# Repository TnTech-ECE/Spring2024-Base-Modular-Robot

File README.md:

# Modular IEEE Robot

## Executive Summary

Each year, Tennessee Technological University (Tech) participates in the Institute of Electrical and Electronics Engineers (IEEE) Southeastern Conference (SECON) hardware competition. The competition asks participants to create a robot that can perform various tasks, and competitors are scored based on their robot’s capability to complete tasks as quickly as possible. In past years, Tech has placed well, but the same problems have arisen each year that have inhibited wins: choppy navigation, shorted cables, and battery depletion are just a few of the many problems teams have repeatedly faced in previous competitions. The team sets out to fix the besetting problems that teams face each year not by competing in SECON, but rather by building a generalized platform that will optimize the basic robotic functionality for future teams. Sensing, movement, and centralized charging are the top priorities in the team’s design, all fitted together in a modular, adaptable framework that can be manipulated to fit most – if not all – IEEE hardware competition specifications. No longer will teams have to spend countless hours learning and designing movement systems or hoping everything works after rewiring a battery mid-competition. The design will take care of these basic competition necessities and leave the custom tailoring to the competition team.  

## Capabilities

The current version of the robot has the following capabilities:
1. Autonomous navigation
2. Modular components that can be easily adapted for different uses
3. Robust, centralized charging system
4. Functioning emergency stop button
5. Can travel inclines and declines up to 25 degrees
7. 360 degrees of movement
8. Knows location within a 2 inch tolerance
9. Sensors are are plug and play adpatable with the use of an I2C bus
10. Foundation layed for autonomous navgivaton with LiDAR and ROS2
11. User manual for teams to understand design considerations, common problems, and solutions

## Salient Outcomes

As projects progress, there are typically outcomes tht are more impressive than others. Here is a list of salient outcomes of this project:
1. Wireless charging proof of concept
2. Multiple navigation subsets for teams to choose between
3. Foundation for layed for ROS2 mapping for future uses
4. Plug and play adapatibility with sensors through I2C buses
5. Power board with ground isolation
6. GUI for teams to see their live data transmission 

## Project Demonstration & Images

3D model of the robot vs the final product

[Watch the video](https://youtu.be/stM9KGa8I_E) of the robot autonomously navigating a line.

[Watch the video](https://youtu.be/3MeIy1WahUA) of the robot autonomously sweeping the board given its location.

[Watch the video](https://youtu.be/3MeIy1WahUA](https://www.youtube.com/watch?v=_iFhnvbLboQ)) of the robot detecting objects in front of it.

## About Us

### Team

**[Luke Chapman](https://www.linkedin.com/in/luke-chapman-/)** is an electrical engineering major at Tennessee Technological University with a minor in mathematics. He is interested in electromagnetics, telecommunications, and signal processing. Luke is responsible for the power management and distribution systems of the robot as well as the experimental wireless power charging system.

**[Reid Crews](https://www.linkedin.com/in/jackson-crews-381187257/)** is an electrical engineering major, mechatronics concentration at Tennessee Technological University with a minor in mathematics. Reid's interests are mechatronics and control systems. For the project, Reid is a contributor for the navigation sensing, primarily the location and object detection subsystems.

**[Isaac Hoese](https://www.linkedin.com/in/isaac-hoese-425748251)** is a senior electrical engineering student from Greeneville, Tn. He is interested in both power system analysis and embedded system design. In this project, Isaac will be a contributor for the navigation sensing, primarily the line following and orientation subsystems.

**[Isaac Jennings](www.linkedin.com/in/isaac-jennings-a04680209)** is a senior electrical engineering student with a minor in mathematics from Church Hill, TN. He takes interest in control systems, programming, and embedded systems, which is where he allocated his time by working on the master control systems on the project. He is responsible for the navigation and localization of the robot as it interfaces with the game board.  

**[Abigail Kennedy](https://www.linkedin.com/in/abigail-kennedy-tech/)** is an electrical engineering major at Tennessee Technological University with minors in mathematics and education. Abigail's primary interest is in controls and PLC design, and for this project, she worked on the motor control subsystem to ensure the robot can move quickly and smoothly.

**[Mabel Olson](https://www.linkedin.com/in/mabelolson/)** is an electrical engineering major at Tennessee Technological University with a minor in mathematics. She is intrested in power and control systems. In this project, Mabel is responsible for the chassis design, robot layout, organization, and any 3D designing of component attachment pieces. 

### Faculty Supervisor

The faculty supervisor for this project is [Dr. Nan Chen][def1]. She completed her electrical and control engineering Bachelor's degree from Nanjing University of Aeronautics and Astronautics. She also completed her Master's and Ph.D. in electrical engineering from the University of Waterloo. 

[def1]: https://www.linkedin.com/in/nan-chen-319aa185/

### Stakeholders

The primary customer for the project is [Professor Jesse Roberts](https://www.linkedin.com/in/jessetnroberts/) - the advisor for the IEEE SECON hardware teams. Future teams are impacted by this design but unable to be stakeholders, so he gives input on their behalf based on his years of experience with the competition.

### Recognitions

We would like to recognize and thank Professor Jesse Roberts, Dr. Nan Chen, and Dr. Charles Van Neste for their continuous input and guidance on the project.

## Repo Organization

### [Reports](/Reports)

The [Project Proposal](./Reports/Project%20Proposal/Project%20Proposal%20Revised.pdf) is the initial document for the project where the problem is defined and the goals for the project.

The [Conceptual Design](./Reports/Conceptual%20Design/Conceptual%20Design%20and%20Planning%20V2.pdf) gives a more detailed solution to the problem as well as subsystem breakdowns and a projected timeline and budget.

The [Experimentation](/Documentation/Experimental%20Analysis) gives the experimental results of the different subsystems and how constraints were met or not.

The [Poster](./Reports/Poster/Modular%20IEEE%20Robot%20Poster.pdf) is what the team presented at the 2024 capstone showcase.

The [Final Presentation](./Reports/Final%20Presentation/Final%20Presentation.pdf) is the presentation that the team gave to the IAB.

The [Lessons Learned](./Reports/LessonsLearnedAndAquiredSkills.md) gives team members' reflections on their progress, oversights, noteable incidents, and successes.

### [Documentation](/Documentation)
All documentation for the project is included in the above folder. Documentation includes all schematics, images, models, BOM, and designs used in the project.

The [Meeting Minutes](/Documentation/Meeting%20Minutes) folder contains the dated minutes from weekly meetings and allows a quick view into the progress of the team.

[Signoffs](/Documentation/Signoffs) are used to finalize designs for each subsystem. This includes schematics, design decisions, BOM, and analysis. 

### [Software](/Software)

 All software used and created is listed in the [Software](./Software) directory. For each subsystem, there are specific folders listed to find the necessary code.

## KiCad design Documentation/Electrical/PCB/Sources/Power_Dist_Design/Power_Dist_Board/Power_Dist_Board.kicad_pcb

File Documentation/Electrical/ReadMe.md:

This directory contains all of the electrical schematics and PCB files. The PCB directory contains files for the simulation, schematics, and design of the power distribution PCB. The Schematics directory contains the files for the Arduino schematic. The Testing directory contains data from testing the battery life and some notes taken while performing tests on the different power subsystems.

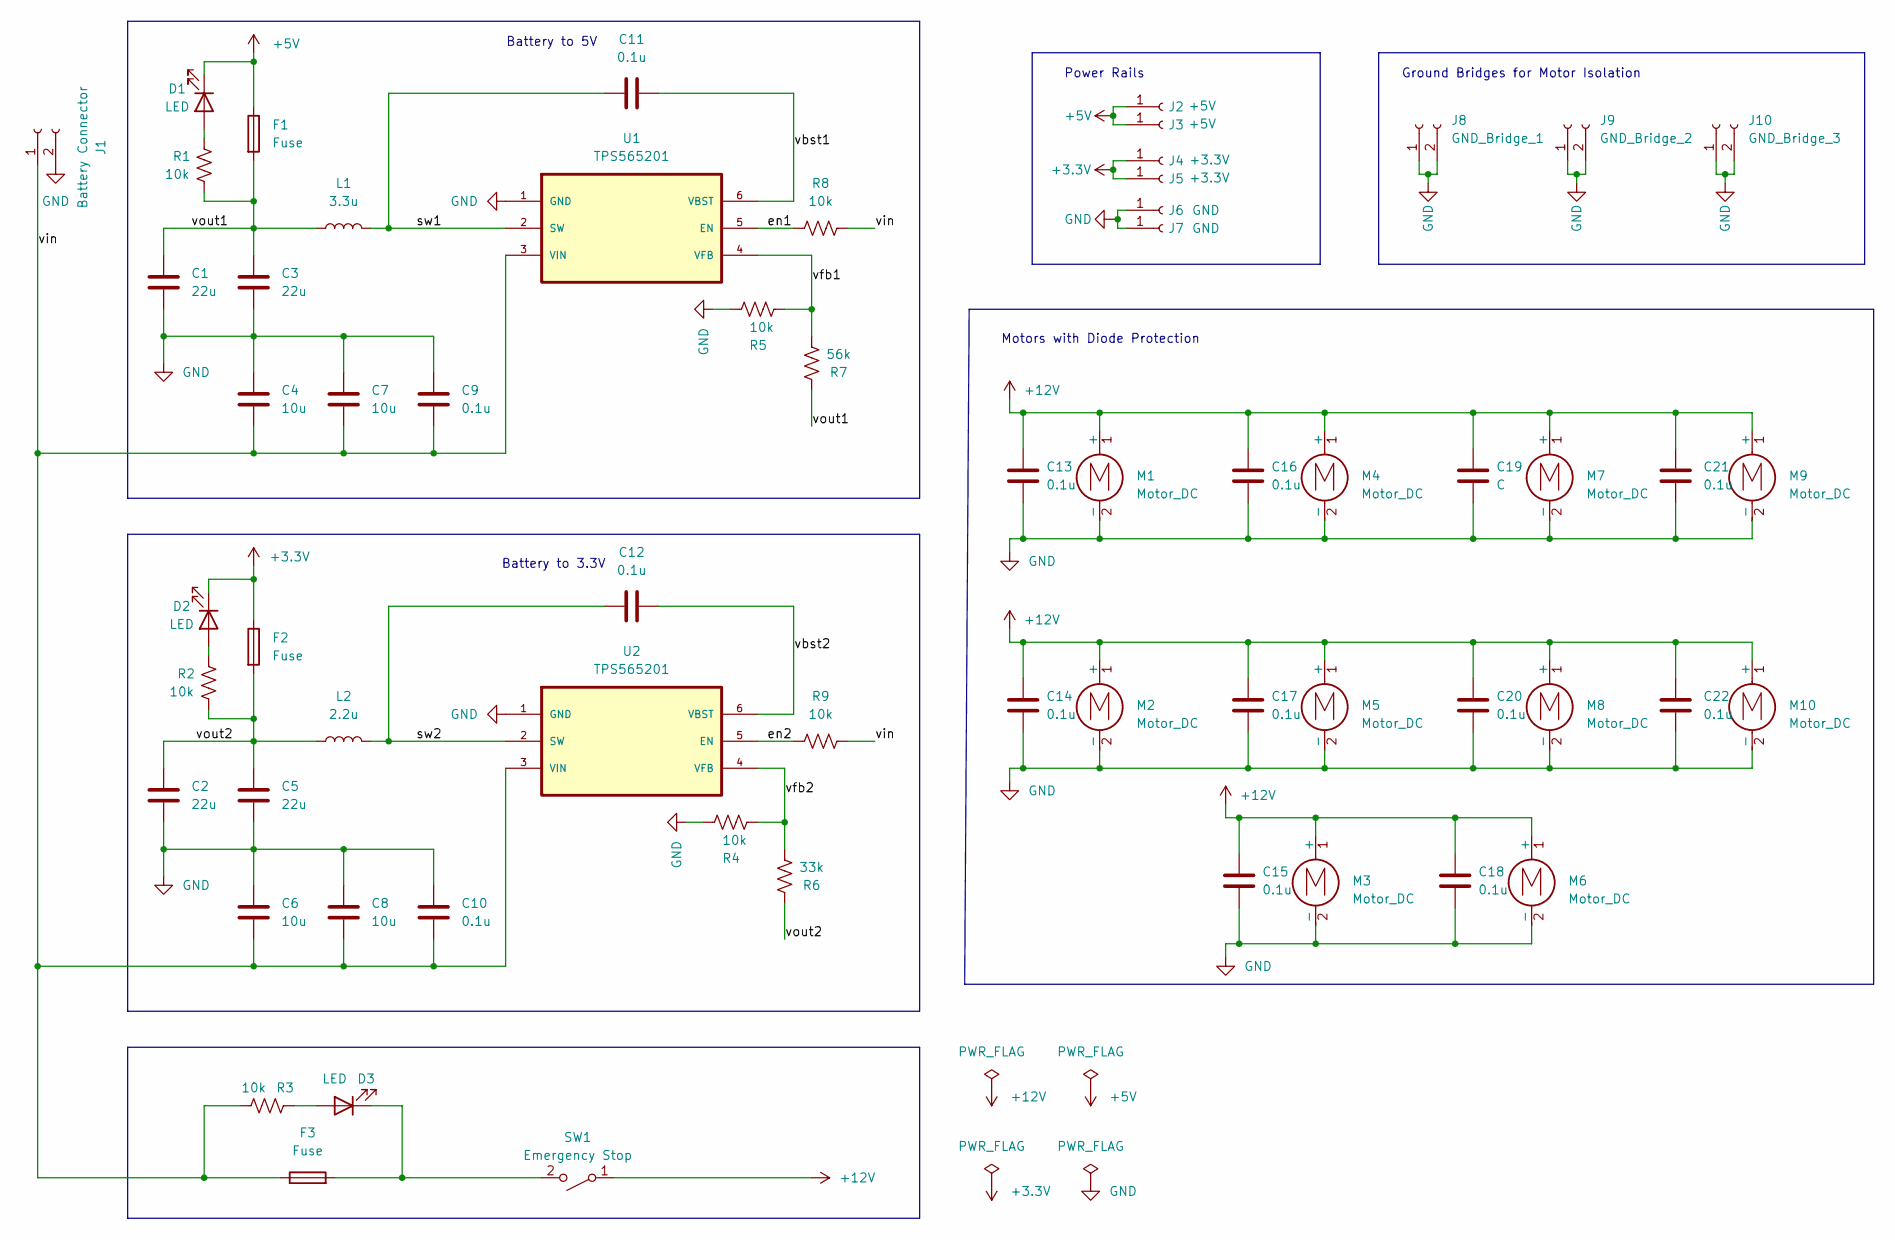
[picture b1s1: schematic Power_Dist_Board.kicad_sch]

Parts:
C1, C2, C3, C5: 22u; C_1206_3216Metric_Pad1.33x1.80mm_HandSolder
C4, C6, C7, C8: 10u; C_1206_3216Metric_Pad1.33x1.80mm_HandSolder
C9, C10, C11, C12, C13, C14, C15, C16, C17, C18, C20, C21, C22: 0.1u; C_1206_3216Metric_Pad1.33x1.80mm_HandSolder
C19: C; C_1206_3216Metric_Pad1.33x1.80mm_HandSolder
D1, D2, D3: LED; LED_1206_3216Metric_Pad1.42x1.75mm_HandSolder
F1, F2, F3: Fuse; Fuse_1206_3216Metric_Pad1.42x1.75mm_HandSolder
J1: Battery Connector; Molex_Screw_Term_0397730002
J2, J3: +5V; Pwr_Rail_Conn_Custom
J4, J5: +3.3V; Pwr_Rail_Conn_Custom
J6, J7: GND; Pwr_Rail_Conn_Custom
J8: GND_Bridge_1; GND_Bridge
J9: GND_Bridge_2; GND_Bridge
J10: GND_Bridge_3; GND_Bridge
L1: 3.3u; IND_SPM6530_TDK
L2: 2.2u; IND_SPM6530_TDK
M1, M2, M3, M4, M5, M6, M7, M8, M9, M10: Motor_DC; Molex_Screw_Term_0397730002
R1, R2, R3, R4, R5, R8, R9: 10k; R_1206_3216Metric_Pad1.30x1.75mm_HandSolder
R6: 33k; R_1206_3216Metric_Pad1.30x1.75mm_HandSolder
R7: 56k; R_1206_3216Metric_Pad1.30x1.75mm_HandSolder
SW1: Emergency Stop; Molex_Screw_Term_0397730002
U1, U2: TPS565201

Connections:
+3.3V: D2.1 (K), F2.1, J4.1, J5.1
+5V: D1.1 (K), F1.1, J2.1, J3.1
+12V: C13.1, C14.1, C15.1, C16.1, C17.1, C18.1, C19.1, C20.1, C21.1, C22.1, M1.1 (+), M2.1 (+), M3.1 (+), M4.1 (+), M5.1 (+), M6.1 (+), M7.1 (+), M8.1 (+), M9.1 (+), M10.1 (+), SW1.1 (A)
/en1: R8.1, U1.5 (EN)
/en2: R9.1, U2.5 (EN)
/sw1: C11.1, L1.2, U1.2 (SW)
/sw2: C12.1, L2.2, U2.2 (SW)
/vbst1: C11.2, U1.6 (VBST)
/vbst2: C12.2, U2.6 (VBST)
/vfb1: R5.2, R7.1, U1.4 (VFB)
/vfb2: R4.2, R6.1, U2.4 (VFB)
/vin: C4.2, C6.2, C7.2, C8.2, C9.2, C10.2, F3.1, J1.1, R3.1, R8.2, R9.2, U1.3 (VIN), U2.3 (VIN)
/vout1: C1.1, C3.1, F1.2, L1.1, R1.1, R7.2
/vout2: C2.1, C5.1, F2.2, L2.1, R2.1, R6.2
GND: C1.2, C2.2, C3.2, C4.1, C5.2, C6.1, C7.1, C8.1, C9.1, C10.1, C13.2, C14.2, C15.2, C16.2, C17.2, C18.2, C19.2, C20.2, C21.2, C22.2, J1.2, J6.1, J7.1, J8.1, J8.2, J9.1, J9.2, J10.1, J10.2, M1.2 (-), M2.2 (-), M3.2 (-), M4.2 (-), M5.2 (-), M6.2 (-), M7.2 (-), M8.2 (-), M9.2 (-), M10.2 (-), R4.1, R5.1, U1.1 (GND), U2.1 (GND)
unnamed: D1.2 (A), R1.2
unnamed: D2.2 (A), R2.2
unnamed: D3.2 (A), R3.2
unnamed: D3.1 (K), F3.2, SW1.2 (B)

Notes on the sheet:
Motors with Diode Protection
Battery to 5V
Battery to 3.3V
Power Rails
Ground Bridges for Motor Isolation

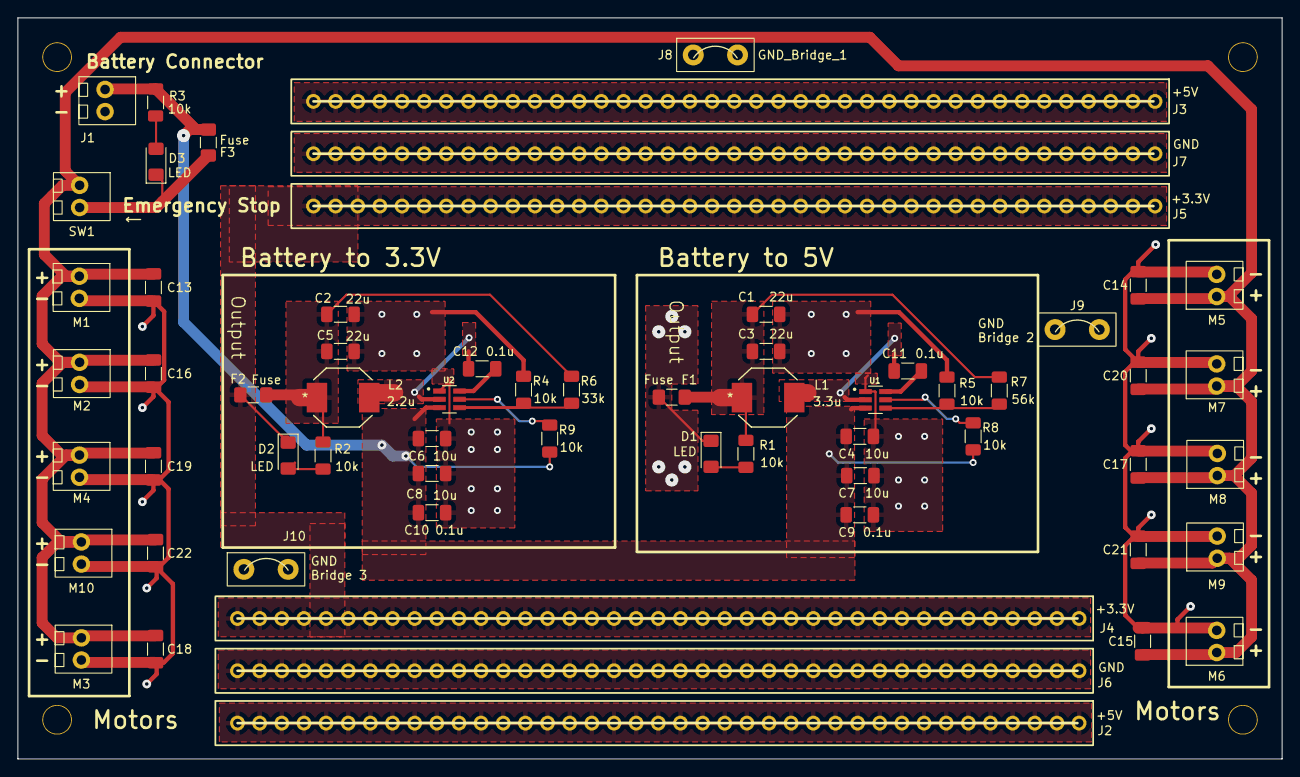
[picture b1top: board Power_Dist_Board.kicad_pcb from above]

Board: 2 copper layers, 145.0 x 85.0 mm, 62 parts (0 on the bottom side), 19 nets.

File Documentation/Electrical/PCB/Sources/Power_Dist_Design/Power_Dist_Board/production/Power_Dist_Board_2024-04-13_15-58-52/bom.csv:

Designator,Footprint,Quantity,Value,LCSC Part #
"C1, C2, C3, C5",1206,4,22u,
"C10, C11, C12, C13, C14, C15, C16, C17, C18, C20, C21, C22, C9",1206,13,0.1u,
C19,1206,1,C,
"C4, C6, C7, C8",1206,4,10u,
"D1, D2, D3",1206,3,LED,
"F1, F2, F3",1206,3,Fuse,
J1,Molex_Screw_Term_0397730002,1,Battery Connector,
J10,GND_Bridge,1,GND_Bridge_3,
"J2, J3",Pwr_Rail_Conn_Custom,2,+5V,
"J4, J5",Pwr_Rail_Conn_Custom,2,+3.3V,
"J6, J7",Pwr_Rail_Conn_Custom,2,GND,
J8,GND_Bridge,1,GND_Bridge_1,
J9,GND_Bridge,1,GND_Bridge_2,
L1,IND_SPM6530_TDK,1,3.3u,
L2,IND_SPM6530_TDK,1,2.2u,
"M1, M10, M2, M3, M4, M5, M6, M7, M8, M9",Molex_Screw_Term_0397730002,10,Motor_DC,
"R1, R2, R3, R4, R5, R8, R9",1206,7,10k,
R6,1206,1,33k,
R7,1206,1,56k,
SW1,Molex_Screw_Term_0397730002,1,Emergency Stop,
"U1, U2",TPS565201,2,TPS565201,

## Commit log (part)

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2023-11-15 Slight changes to pcb
2023-11-15 pcb autosave
2023-11-15 Updated signoff in response to feedback
2023-11-15 Fixed singular citation
2023-11-17 Added pictures
2023-11-18 Changed ground plane and added jumpers to motor-ground and ground connection
2023-11-18 Removed accidental battery signoff document from main branch
2023-11-18 Finalized pcb
2023-11-20 Removed conflicting pcb files
2023-11-21 Added 11/21/23 meeting minutes
2023-11-21 Added screw holes to board and generated gerber file
2023-11-24 Images Update
2023-11-24 Images
2023-11-24 Adding CAD Files
2023-11-24 Reduced length by 5mm to fit in chassis
2023-11-28 Added to wireless charging signoff
2023-11-28 Reorganization
2023-11-28 Removed redundant folder
2023-11-28 Removed extra csv file
2023-11-28 Removed minutes readme and minutes template
2023-11-29 Organizing the Github
2023-11-30 Rename reidcrews-signoff-ObjectDetection.md to ReidCrews-signoff-ObjectDetection.md
2023-11-30 Rename ReidCrews-signoff-Location.md to ReidCrews-Signoff-Location.md
2023-11-30 Changed signoff names
2023-11-30 Fixed image paths in signoffs
2023-11-30 Added bio section to main readme
2023-12-12 Added keepout zones under inductors that were accidentally removed at some point
2024-01-22 Removed conflicting old versions of pcb files
2024-01-28 A few small changes to WPT charging signoff
2024-01-30 added meeting minutes for 1/29
2024-01-30 Added meeting minutes 1/30
2024-02-01 small changes
2024-02-03 Added notes from testing the pcb, battery, and charger
2024-02-05 changed WPT signoff name
2024-02-05 Added meeting minutes for 2/5/24
2024-02-06 Added Testing File For Line Following
    Created a testing file with blue and yellow lines with varying widths against a white backdrop to determine the threshold of the reflectance array.
2024-02-08 Added meeting minutes 2/8/24
2024-02-12 Added meeting minutes 2/12/24
2024-02-13 added advisor meeting minutes for 2/13/24
2024-02-14 Isaac H Nav Code
    Code for orientation, line following, and OLED
2024-02-14 Added minimally functional prototype checklist
2024-02-19 Added meeting minutes 2/19
2024-02-21 added meeting minutes 2/20/24
2024-02-22 Added testing notes from 2/22/24
2024-02-23 Update IsaacH_Nav2.h
    Change initialize sensor function and add description to run object detection sensor function.
2024-02-26 Added meeting minutes 2/26/24
2024-02-28 Update Nav-Microcontroller-Signoff.md
    Changed the library link for Obj Detect
2024-02-28 added meeting minutes for tomorrow 2/29/24 with notes from today
2024-03-01 Update IsaacH_Nav2.h
    Updated .h file
2024-03-01 Added meeting minutes 2/29/24 and added folder for MFP
2024-03-04 added meeting minutes 3/4/24
2024-03-16 added 'meeting minutes' during spring break
2024-03-18 added meeting minutes 3/18/24
2024-03-18 Add files via upload
    Added an updated schematic for motor control to show the fix for pin 4 not working
2024-03-18 Update AbigailKennedy-Signoff-MotorControl.md
    Showing new schematic photo
2024-03-20 Added meeting minutes for 3/19/24
2024-03-20 renamed meeting minutes
2024-03-22 added 2 videos for experimental analysis
2024-03-23 added table
2024-03-24 added plug-minus to battery terminal
2024-03-24 backing up in case of changes
2024-03-25 added meeting minutes for 3/25/24
2024-03-27 added meeting minutes 3/26/24
2024-04-01 EA Updates
2024-04-01 added meeting minutes 4/1/24
2024-04-01 Update Experimental Analysis.md
    Fixed formatting
2024-04-01 Update Experimental Analysis.md
    Added hyperlinks to tables
2024-04-02 added to EA document and fixed image links
2024-04-02 added more videos
2024-04-03 added to EA doc
2024-04-03 Photos
2024-04-04 Adding Location Tables for EA Doc
2024-04-04 added to ea doc constraint 5
2024-04-04 Added meeting minutes 4/4/24
2024-04-06 slight change to meeting minutes
2024-04-08 Update Experimental Analysis.md with incline/decline
2024-04-08 added meeting minutes 4/8/24
2024-04-09 Create 2023_Board
2024-04-09 Create LineFollowing2023Board
2024-04-09 added WPT video
2024-04-09 added WPT to EA
2024-04-09 added very rough estimate to battery life
2024-04-09 Update 2023_Board
2024-04-09 Update LineFollowing2023Board
2024-04-13 added battery data and plots
2024-04-13 changed plot color
2024-04-13 added battery life estimate
2024-04-13 added about battery life estimation
2024-04-13 added 3d models to pcb
2024-04-13 small changes to power pcb
2024-04-13 generated new gerber
2024-04-13 all 3d models added to board
2024-04-13 generated gerber
2024-04-14 tried to export 3d model to blender, didn't work. Also got image of pcb
2024-04-23 added stuff to pcb or regenerated gerbers
2024-04-23 added poster and to lessons learned
2024-04-23 added to readme
2024-04-24 added to learned lessons
2024-04-24 added schematic of power board as pdf
2024-04-24 changed link to experimentation
2024-04-24 added indiv presentation
2024-04-24 added readme to spice sim
2024-04-24 added to lessons learned
2024-04-25 Update LessonsLearnedAndAquiredSkills.md
    Added spots for classes used
2024-04-25 3D models
2024-04-25 maybe fixed link
2024-04-25 fixed link
2024-04-25 Jetson_code
2024-04-25 added link to software
2024-04-25 added ros stuff
2024-04-25 jetson_stuff_2
2024-04-25 Moved BOM
2024-04-25 electrical readme
2024-04-25 added pres as pdf
2024-04-26 power board destructive arduino file
2024-04-26 added link to software directory
2024-05-01 added manuals folder
2024-05-05 added to manual readme
2024-05-05 added power dist manual
2024-05-05 added missing figure title
2024-05-05 added battery management manual
2024-05-05 added updated final pres
2024-05-05 added wireless charging manual
